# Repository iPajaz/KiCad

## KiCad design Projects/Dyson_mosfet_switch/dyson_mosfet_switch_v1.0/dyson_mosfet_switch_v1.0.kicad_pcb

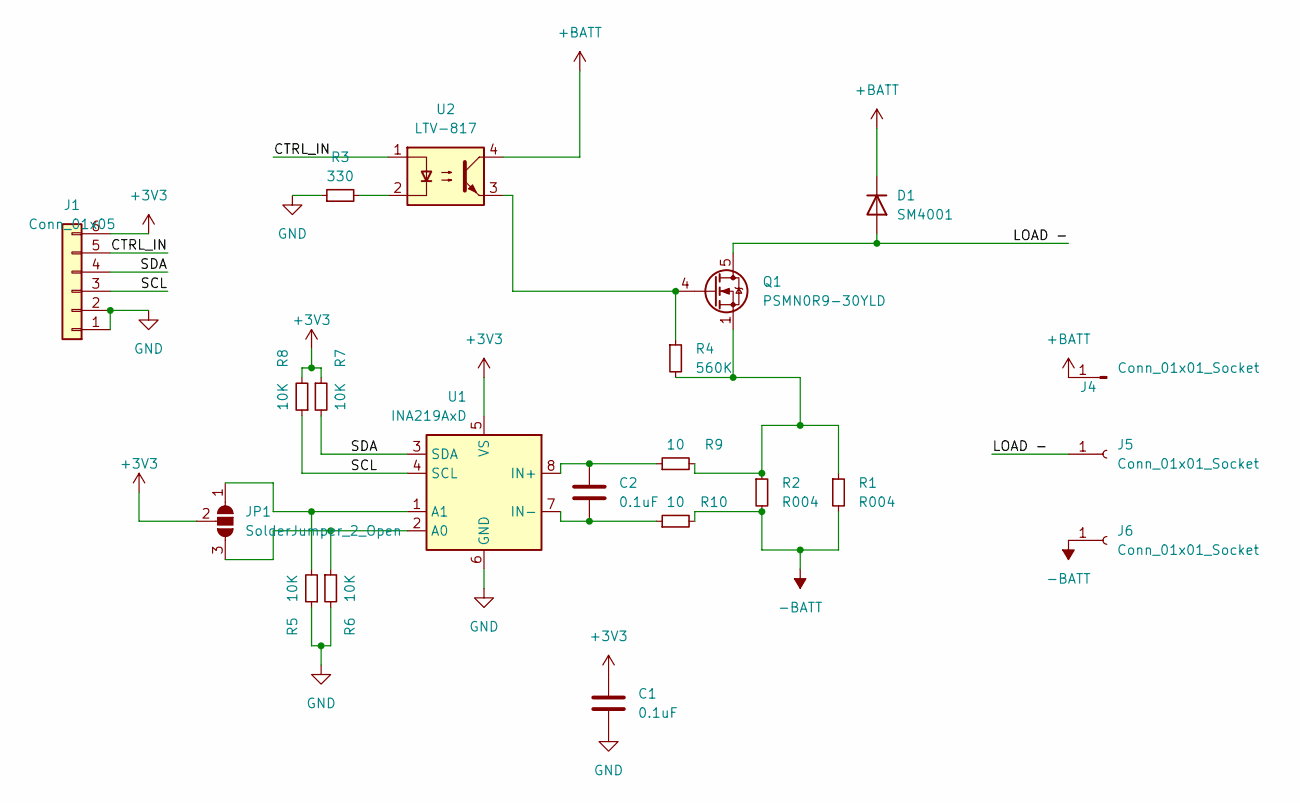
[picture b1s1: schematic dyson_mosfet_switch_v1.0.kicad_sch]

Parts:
C1, C2: 0.1uF; C_0805_2012Metric
D1: SM4001; D_SMA
J1: Conn_01x05; JST_PH_B6B-PH-K_1x06_P2.00mm_Vertical
J4: Conn_01x01_Socket; PinHeader_1x01_P2.54mm_Vertical
J5, J6: Conn_01x01_Socket; MountingHole_5mm_Pad_Via
JP1: SolderJumper_2_Open; SolderJumper-3_P1.3mm_Open_RoundedPad1.0x1.5mm
Q1: PSMN0R9-30YLD; LFPAK56
R1, R2: R004; R_2816_7142Metric
R3: 330; R_1206_3216Metric
R4: 560K; R_1206_3216Metric
R5, R6, R7, R8: 10K; R_1206_3216Metric
R9, R10: 10; R_1206_3216Metric
U1: INA219AxD; SOIC-8_3.9x4.9mm_P1.27mm
U2: LTV-817; DIP-4_W7.62mm

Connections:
+3V3: C1.1, J1.6, JP1.2 (C), R7.1, R8.2, U1.5 (VS)
+BATT: D1.1 (K), J4.1, U2.4
-BATT: J6.1, R1.2, R2.2, R10.2
/CTRL_IN: J1.5, U2.1
/LOAD -: D1.2 (A), J5.1, Q1.5 (D)
/SCL: J1.3, R8.1, U1.4 (SCL)
/SDA: J1.4, R7.2, U1.3 (SDA)
GND: C1.2, J1.1, J1.2, R3.1, R5.1, R6.2, U1.6 (GND)
unnamed: JP1.1 (A), R5.2, U1.1 (A1)
unnamed: JP1.3 (B), R6.1, U1.2 (A0)
unnamed: Q1.4 (G), R4.1, U2.3
unnamed: Q1.1 (S), Q1.2 (S), Q1.3 (S), R1.1, R2.1, R4.2, R9.2
unnamed: R3.2, U2.2
unnamed: C2.1, R9.1, U1.8 (IN+)
unnamed: C2.2, R10.1, U1.7 (IN-)

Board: 2 copper layers, 21 parts (0 on the bottom side), 15 nets, no tracks yet.

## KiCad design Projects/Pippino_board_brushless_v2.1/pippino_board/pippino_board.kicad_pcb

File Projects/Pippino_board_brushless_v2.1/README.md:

# Pippino II control PCB v2.1

## Main Features:

### Power supply

The board supports a 12 V power supply (within the range provided by a 3S Li-Ion battery), which is distributed to:
- A completely independent 3.3 V DC-DC converter providing always-on power supply, used to power the on-board E18 ZigBee module.
- A gated 12 V net, that can be switched on via a low on-resistance AO4409 MOSFET

The 12 V net, subsequently, provides power to:
- 4A, 5 V DC-DC converter used to output power to an external SBC (e.g. a Jetson Nano)
- 12 V output connector, to supply external peripherals, such as an USB splitter
- on board 3.3 V DC-DC converter, used to power the on-board ESP32-S3 microcontroller

### Always-on, low-power ZigBee module

The board includes an always-on ZigBee module, enabling the robot to be woken up via ZigBee/Home automation
while consuming low power (~10mA) when the system is powered off.
The ZigBee module can be programmed to perform more complex actions if required (GPIO pins exposed with a connector).

### ESP32-S3 microcontroller

The board includes an ESP32-S3 microcontroller with BT/WiFi capability. The ESP32 can be programmed via the USB3 connector,
which is intended to be always connected to the SBC.
OTA programming is then not required, as the SBC can be used to reprogram the ESP32 at any time.

The ESP32 is used to control the main driving motors for the robot, as well as receive information from sensors etc.

### Peripherals

The board includes:
- An ADC chip, connected via I2C to the MCU
- Smart DC-DC converters (TPS62110) with low battery voltage flagging capability (connected to a pin of the MCU)
- CP2102N USB to serial converter (for communication with the MCU)
- IO expansion IC connected via I2C + Interrupt

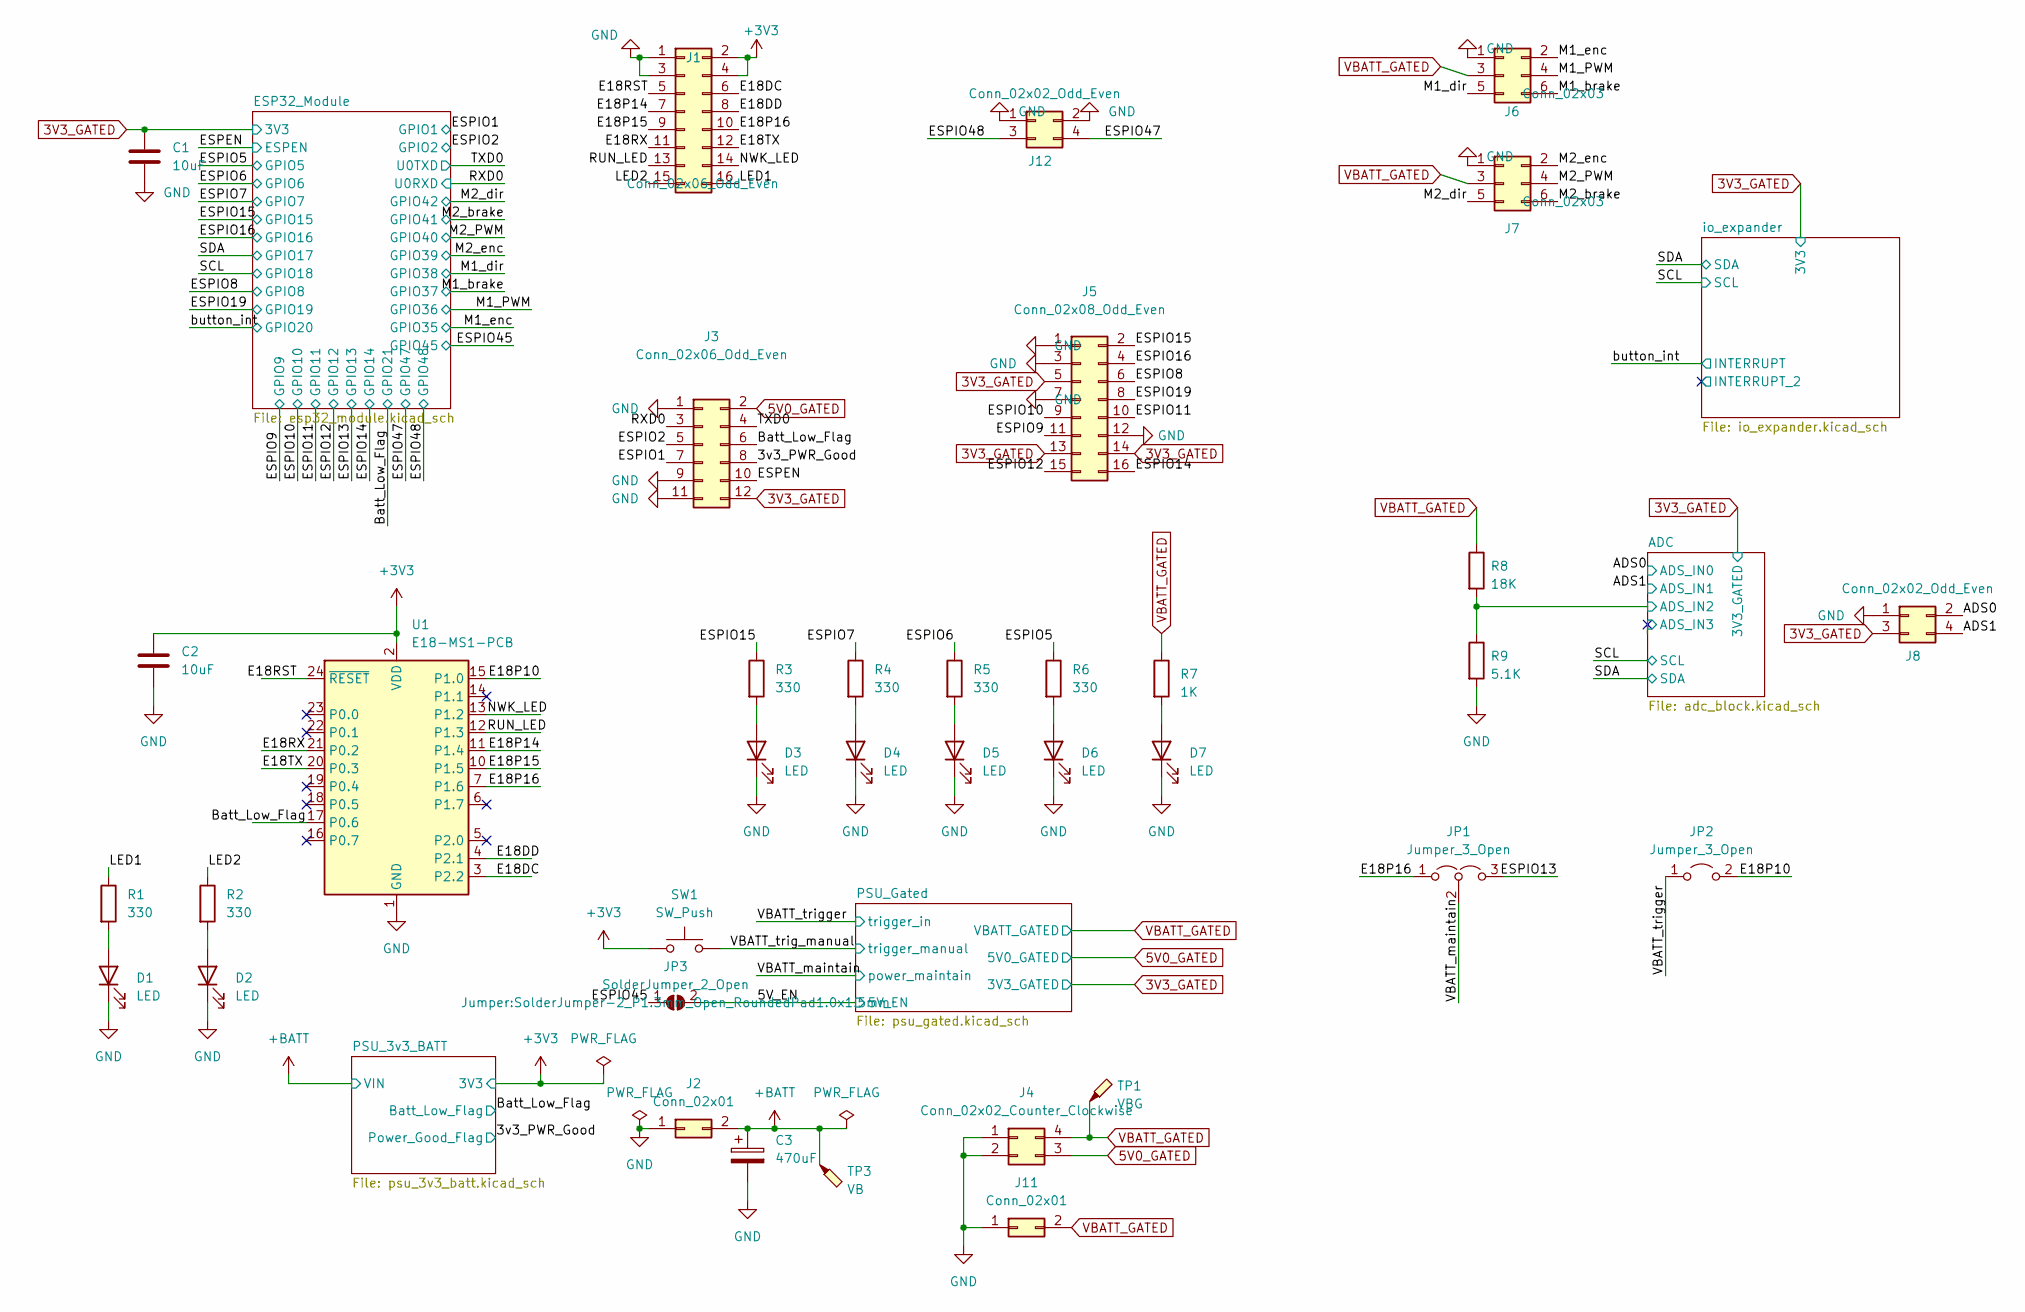
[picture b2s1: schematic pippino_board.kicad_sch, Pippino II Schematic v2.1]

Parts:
C1, C2: 10uF; C_0805_2012Metric
C3: 470uF; CP_Elec_10x10.5
D1, D2, D3, D4, D5, D6, D7: LED; LED_1206_3216Metric
J1: Conn_02x06_Odd_Even; PinHeader_2x08_P2.54mm_Vertical
J2, J11: Conn_02x01; Molex_Micro-Fit_3.0_43045-0200_2x01_P3.00mm_Horizontal
J3: Conn_02x06_Odd_Even; PinHeader_2x06_P2.54mm_Vertical
J4: Conn_02x02_Counter_Clockwise; Molex_Micro-Fit_3.0_43045-0400_2x02_P3.00mm_Horizontal
J5: Conn_02x08_Odd_Even; PinHeader_2x08_P2.54mm_Vertical
J6, J7: Conn_02x03; PinHeader_2x03_P2.54mm_Vertical
J8, J12: Conn_02x02_Odd_Even; PinHeader_2x02_P2.54mm_Vertical
JP1: Jumper_3_Open; PinHeader_1x03_P2.54mm_Vertical
JP2: Jumper_3_Open; PinHeader_1x02_P2.54mm_Vertical
JP3: SolderJumper_2_Open; SolderJumper-2_P1.3mm_Open_RoundedPad1.0x1.5mm
R1, R2, R3, R4, R5, R6: 330; R_1206_3216Metric
R7: 1K; R_1206_3216Metric
R8: 18K; R_1206_3216Metric
R9: 5.1K; R_1206_3216Metric
SW1: SW_Push; SW_SPST_CK_RS282G05A3
TP1: VBG; TestPoint_Pad_D1.5mm
TP3: VB; TestPoint_Pad_D1.5mm
U1: E18-MS1-PCB

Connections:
3V3_GATED: C1.1, J3.12, J5.5, J5.13, J5.14, J8.3; also elsewhere on the board
5V0_GATED: J3.2, J4.3; also elsewhere on the board
+3V3: C2.1, J1.2, J1.4, SW1.1, U1.2 (VDD); also elsewhere on the board
+BATT: C3.1, J2.2, TP3.1; also elsewhere on the board
/3v3_PWR_Good: J3.8; also elsewhere on the board
/5V_EN: JP3.2 (B); also elsewhere on the board
/ADC/ADS_IN2: R8.2, R9.1; also elsewhere on the board
/ADS0: J8.2; also elsewhere on the board
/ADS1: J8.4; also elsewhere on the board
/Batt_Low_Flag: J3.6, U1.17 (P0.6); also elsewhere on the board
/E18DC: J1.6, U1.3 (P2.2)
/E18DD: J1.8, U1.4 (P2.1)
/E18P10: JP2.2 (B), U1.15 (P1.0)
/E18P14: J1.7, U1.11 (P1.4)
/E18P15: J1.9, U1.10 (P1.5)
/E18P16: J1.10, JP1.1 (A), U1.7 (P1.6)
/E18RST: J1.5, U1.24 (~RESET)
/E18RX: J1.11, U1.21 (P0.2)
/E18TX: J1.12, U1.20 (P0.3)
/ESPEN: J3.10; also elsewhere on the board
/ESPIO1: J3.7; also elsewhere on the board
/ESPIO2: J3.5; also elsewhere on the board
/ESPIO5: R6.1; also elsewhere on the board
/ESPIO6: R5.1; also elsewhere on the board
/ESPIO7: R4.1; also elsewhere on the board
/ESPIO8: J5.6; also elsewhere on the board
/ESPIO9: J5.11; also elsewhere on the board
/ESPIO10: J5.9; also elsewhere on the board
/ESPIO11: J5.10; also elsewhere on the board
/ESPIO12: J5.15; also elsewhere on the board
/ESPIO13: JP1.3 (B); also elsewhere on the board
/ESPIO14: J5.16; also elsewhere on the board
/ESPIO15: J5.2, R3.1; also elsewhere on the board
/ESPIO16: J5.4; also elsewhere on the board
/ESPIO19: J5.8; also elsewhere on the board
/ESPIO45: JP3.1 (A); also elsewhere on the board
/ESPIO47: J12.4; also elsewhere on the board
/ESPIO48: J12.3; also elsewhere on the board
/LED1: J1.16, R1.1
/LED2: J1.15, R2.1
/M1_PWM: J6.4; also elsewhere on the board
/M1_brake: J6.6; also elsewhere on the board
/M1_dir: J6.5; also elsewhere on the board
/M1_enc: J6.2; also elsewhere on the board
/M2_PWM: J7.4; also elsewhere on the board
/M2_brake: J7.6; also elsewhere on the board
/M2_dir: J7.5; also elsewhere on the board
/M2_enc: J7.2; also elsewhere on the board
/NWK_LED: J1.14, U1.13 (P1.2)
/RUN_LED: J1.13, U1.12 (P1.3)
/RXD0: J3.3; also elsewhere on the board
/TXD0: J3.4; also elsewhere on the board
/VBATT_maintain: JP1.2 (C); also elsewhere on the board
/VBATT_trig_manual: SW1.2; also elsewhere on the board
/VBATT_trigger: JP2.1 (A); also elsewhere on the board
unnamed: D1.2 (A), R1.2
unnamed: D2.2 (A), R2.2
unnamed: D3.2 (A), R3.2
unnamed: D4.2 (A), R4.2
unnamed: D5.2 (A), R5.2
unnamed: D6.2 (A), R6.2
unnamed: D7.2 (A), R7.2
VBATT_GATED: J4.4, J6.3, J7.3, J11.2, R7.1, R8.1, TP1.1; also elsewhere on the board

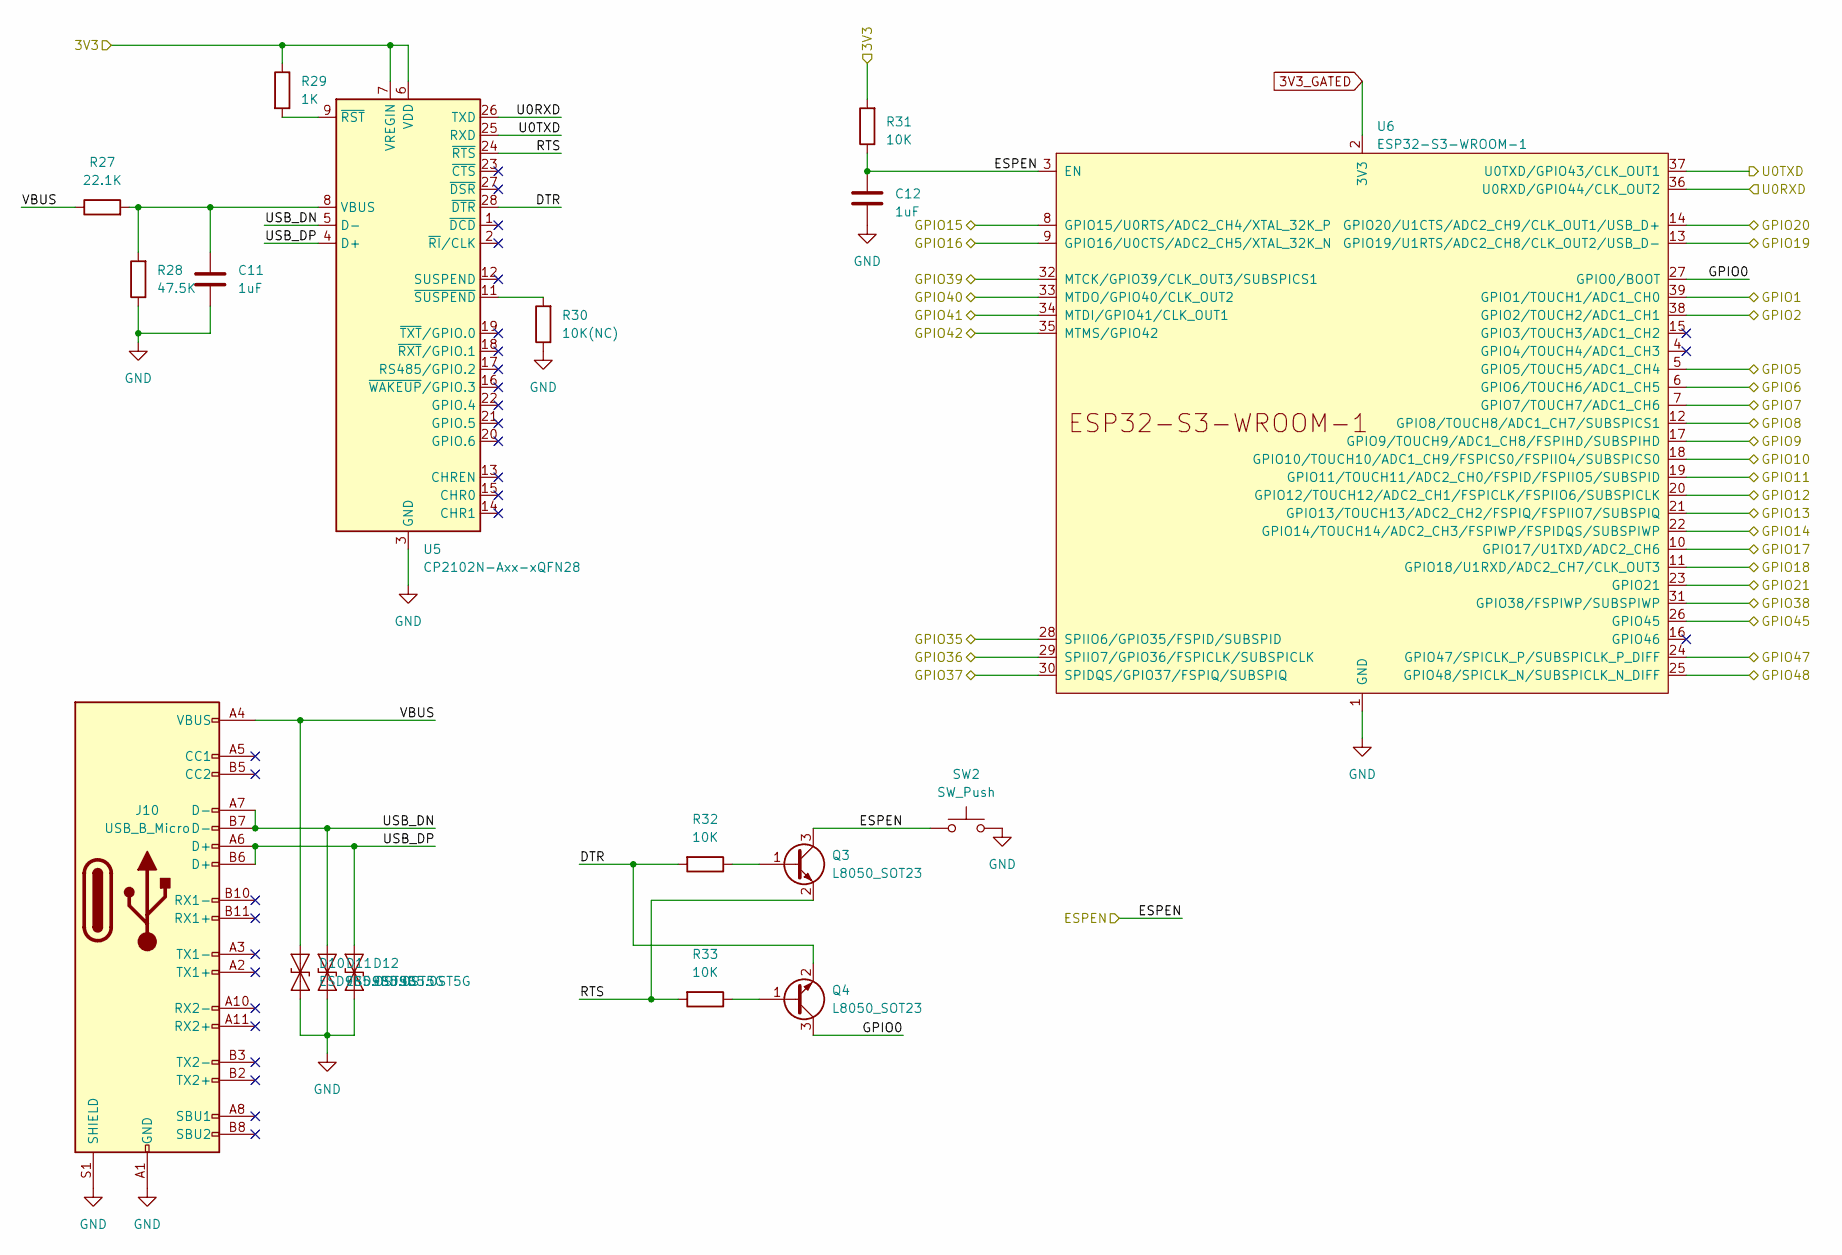
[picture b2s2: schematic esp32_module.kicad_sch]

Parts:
C11, C12: 1uF; C_0805_2012Metric
D10, D11, D12: ESD9B5.0ST5G; D_SOD-523
J10: USB_B_Micro; USB_C_Receptacle_Amphenol_12401610E4-2A
Q3, Q4: L8050_SOT23; SOT-23
R27: 22.1K; R_1206_3216Metric
R28: 47.5K; R_1206_3216Metric
R29: 1K; R_1206_3216Metric
R30: 10K(NC); R_1206_3216Metric
R31, R32, R33: 10K; R_1206_3216Metric
SW2: SW_Push; SW_SPST_CK_RS282G05A3
U5: CP2102N-Axx-xQFN28; QFN-28-1EP_5x5mm_P0.5mm_EP3.35x3.35mm
U6: ESP32-S3-WROOM-1

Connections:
3V3_GATED: R29.1, R31.2, U5.6 (VDD), U5.7 (VREGIN), U6.2 (3V3); also elsewhere on the board
/Batt_Low_Flag: U6.23 (GPIO21); also elsewhere on the board
/ESP32_Module/DTR: Q4.2 (E), R32.2, U5.28 (~DTR)
/ESP32_Module/GPIO0: Q4.3 (C), U6.27 (GPIO0/BOOT)
/ESP32_Module/RTS: Q3.2 (E), R33.2, U5.24 (~RTS)
/ESP32_Module/USB_DN: D11.1 (A1), J10.A7 (D-), J10.B7 (D-), U5.5 (D-)
/ESP32_Module/USB_DP: D12.1 (A1), J10.A6 (D+), J10.B6 (D+), U5.4 (D+)
/ESP32_Module/VBUS: D10.1 (A1), J10.A4 (VBUS), J10.A9 (VBUS), J10.B4 (VBUS), J10.B9 (VBUS), R27.1
/ESPEN: C12.1, Q3.3 (C), R31.1, SW2.1, U6.3 (EN); also elsewhere on the board
/ESPIO1: U6.39 (GPIO1/TOUCH1/ADC1_CH0); also elsewhere on the board
/ESPIO2: U6.38 (GPIO2/TOUCH2/ADC1_CH1); also elsewhere on the board
/ESPIO5: U6.5 (GPIO5/TOUCH5/ADC1_CH4); also elsewhere on the board
/ESPIO6: U6.6 (GPIO6/TOUCH6/ADC1_CH5); also elsewhere on the board
/ESPIO7: U6.7 (GPIO7/TOUCH7/ADC1_CH6); also elsewhere on the board
/ESPIO8: U6.12 (GPIO8/TOUCH8/ADC1_CH7/SUBSPICS1); also elsewhere on the board
/ESPIO9: U6.17 (GPIO9/TOUCH9/ADC1_CH8/FSPIHD/SUBSPIHD); also elsewhere on the board
/ESPIO10: U6.18 (GPIO10/TOUCH10/ADC1_CH9/FSPICS0/FSPIIO4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); also elsewhere on the board
/ESPIO11: U6.19 (GPIO11/TOUCH11/ADC2_CH0/FSPID/FSPIIO5/S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); also elsewhere on the board
/ESPIO12: U6.20 (GPIO12/TOUCH12/ADC2_CH1/FSPICLK/FSPIIO6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); also elsewhere on the board
/ESPIO13: U6.21 (GPIO13/TOUCH13/ADC2_CH2/FSPIQ/FSPIIO7/S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); also elsewhere on the board
/ESPIO14: U6.22 (GPIO14/TOUCH14/ADC2_CH3/FSPIWP/FSPIDQS/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); also elsewhere on the board
/ESPIO15: U6.8 (GPIO15/U0RTS/ADC2_CH4/XTAL_32K_P); also elsewhere on the board
/ESPIO16: U6.9 (GPIO16/U0CTS/ADC2_CH5/XTAL_32K_N); also elsewhere on the board
/ESPIO19: U6.13 (GPIO19/U1RTS/ADC2_CH8/CLK_OUT2/USB_D-); also elsewhere on the board
/ESPIO45: U6.26 (GPIO45); also elsewhere on the board
/ESPIO47: U6.24 (GPIO47/SPICLK_P/SUBSPICLK_P_DIFF); also elsewhere on the board
/ESPIO48: U6.25 (GPIO48/SPICLK_N/SUBSPICLK_N_DIFF); also elsewhere on the board
/M1_PWM: U6.29 (SPIIO7/GPIO36/FSPICLK/SUBSPICLK); also elsewhere on the board
/M1_brake: U6.30 (SPIDQS/GPIO37/FSPIQ/SUBSPIQ); also elsewhere on the board
/M1_dir: U6.31 (GPIO38/FSPIWP/SUBSPIWP); also elsewhere on the board
/M1_enc: U6.28 (SPIIO6/GPIO35/FSPID/SUBSPID); also elsewhere on the board
/M2_PWM: U6.33 (MTDO/GPIO40/CLK_OUT2); also elsewhere on the board
/M2_brake: U6.34 (MTDI/GPIO41/CLK_OUT1); also elsewhere on the board
/M2_dir: U6.35 (MTMS/GPIO42); also elsewhere on the board
/M2_enc: U6.32 (MTCK/GPIO39/CLK_OUT3/SUBSPICS1); also elsewhere on the board
/RXD0: U5.26 (TXD), U6.36 (U0RXD/GPIO44/CLK_OUT2); also elsewhere on the board
/SCL: U6.11 (GPIO18/U1RXD/ADC2_CH7/CLK_OUT3); also elsewhere on the board
/SDA: U6.10 (GPIO17/U1TXD/ADC2_CH6); also elsewhere on the board
/TXD0: U5.25 (RXD), U6.37 (U0TXD/GPIO43/CLK_OUT1); also elsewhere on the board
/button_int: U6.14 (GPIO20/U1CTS/ADC2_CH9/CLK_OUT1/USB_D+); also elsewhere on the board
unnamed: Q3.1 (B), R32.1
unnamed: Q4.1 (B), R33.1
unnamed: C11.1, R27.2, R28.2, U5.8 (VBUS)
unnamed: R29.2, U5.9 (~RST)
unnamed: R30.2, U5.11 (~SUSPEND)

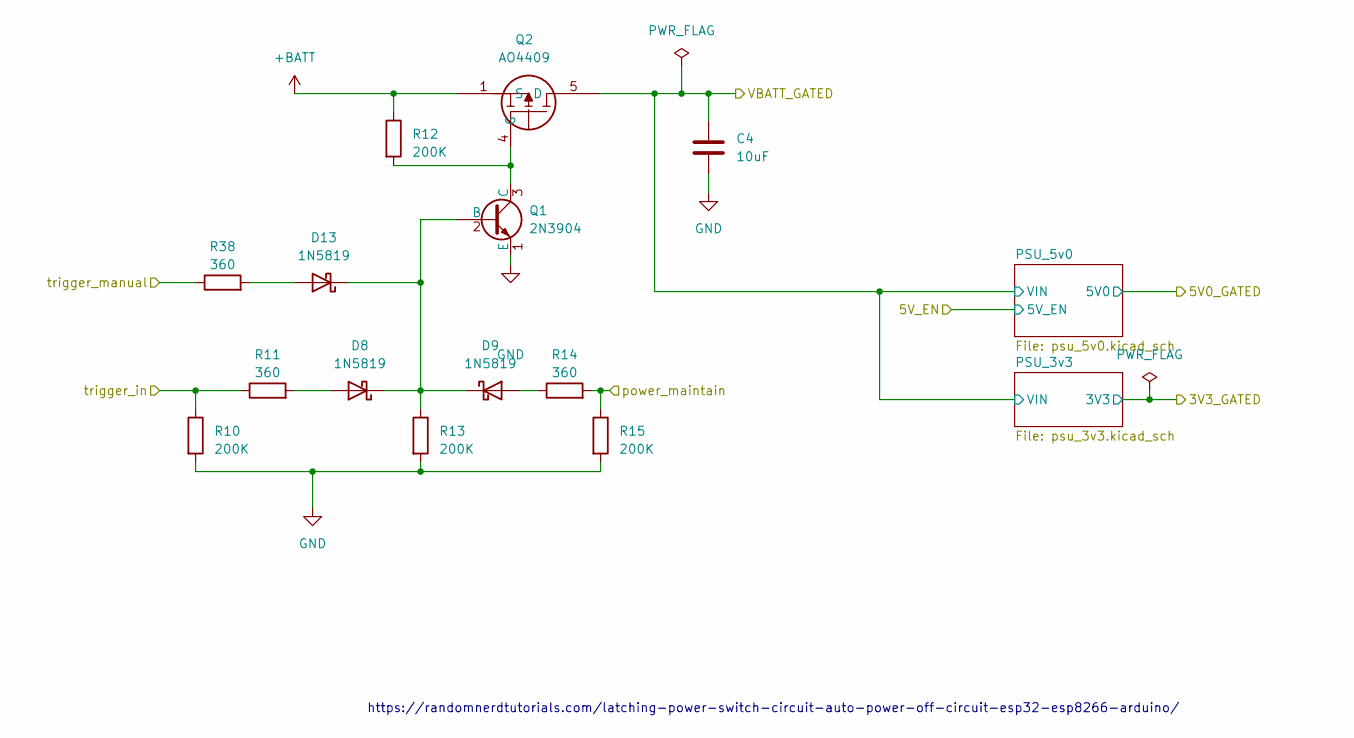
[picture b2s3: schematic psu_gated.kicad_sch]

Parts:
C4: 10uF; C_0805_2012Metric
D8, D9, D13: 1N5819; D_SOD-123
Q1: 2N3904; 2N3904_SOT-23
Q2: AO4409; SOIC-8_3.9x4.9mm_P1.27mm
R10, R12, R13, R15: 200K; R_1206_3216Metric
R11, R14, R38: 360; R_1206_3216Metric

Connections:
+BATT: Q2.1 (S), Q2.2 (S), Q2.3 (S), R12.1; also elsewhere on the board
/VBATT_maintain: R14.2, R15.1; also elsewhere on the board
/VBATT_trig_manual: R38.1; also elsewhere on the board
/VBATT_trigger: R10.1, R11.1; also elsewhere on the board
unnamed: D8.2 (A), R11.2
unnamed: D9.2 (A), R14.1
unnamed: D13.2 (A), R38.2
unnamed: D8.1 (K), D9.1 (K), D13.1 (K), Q1.2 (B), R13.1
unnamed: Q1.3 (C), Q2.4 (G), R12.2
VBATT_GATED: C4.1, Q2.5 (D), Q2.6 (D), Q2.7 (D), Q2.8 (D); also elsewhere on the board

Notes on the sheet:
https://randomnerdtutorials.com/latching-power-switch-circuit-auto-power-off-circuit-esp32-esp8266-arduino/

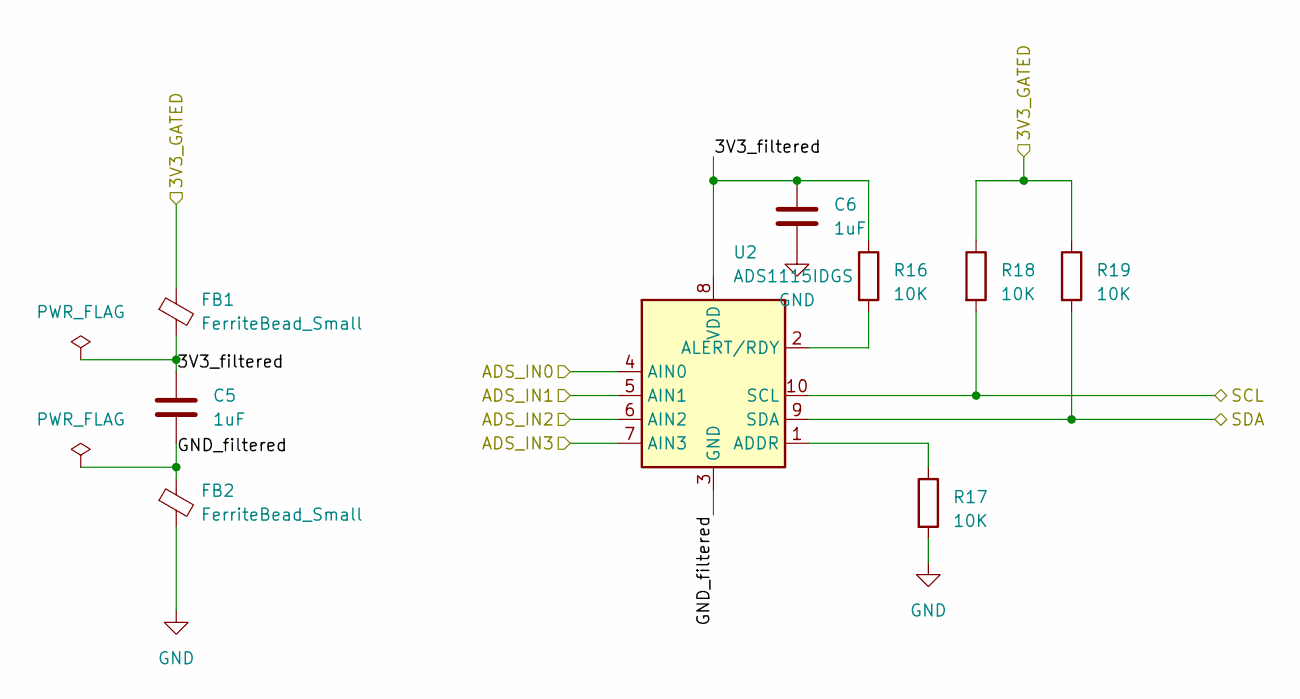
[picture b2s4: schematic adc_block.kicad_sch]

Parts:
C5, C6: 1uF; C_0805_2012Metric
FB1, FB2: FerriteBead_Small; C_0805_2012Metric
R16, R17, R18, R19: 10K; R_1206_3216Metric
U2: ADS1115IDGS; VSSOP-10_3x3mm_P0.5mm

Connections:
3V3_GATED: FB1.1, R18.1, R19.1; also elsewhere on the board
/ADC/3V3_filtered: C5.1, C6.1, FB1.2, R16.1, U2.8 (VDD)
/ADC/ADS_IN2: U2.6 (AIN2); also elsewhere on the board
/ADC/ADS_IN3: U2.7 (AIN3)
/ADC/GND_filtered: C5.2, FB2.1, U2.3 (GND)
/ADS0: U2.4 (AIN0); also elsewhere on the board
/ADS1: U2.5 (AIN1); also elsewhere on the board
/SCL: R18.2, U2.10 (SCL); also elsewhere on the board
/SDA: R19.2, U2.9 (SDA); also elsewhere on the board
unnamed: R17.1, U2.1 (ADDR)
unnamed: R16.2, U2.2 (ALERT/RDY)

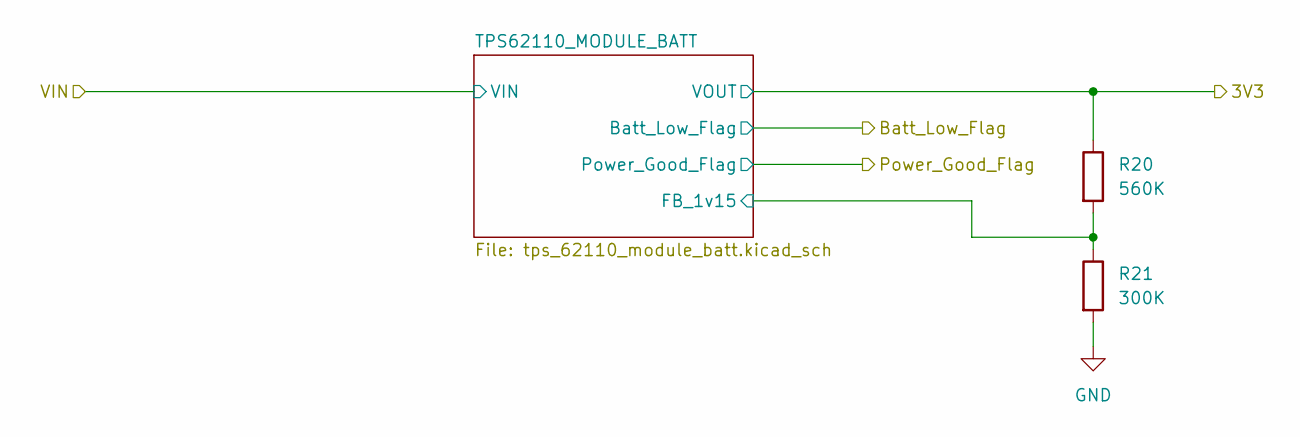
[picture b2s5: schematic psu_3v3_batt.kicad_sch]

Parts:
R20: 560K; R_1206_3216Metric
R21: 300K; R_1206_3216Metric

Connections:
+3V3: R20.1; also elsewhere on the board
/PSU_3v3_BATT/TPS62110_MODULE_BATT/FB_1v15: R20.2, R21.1; also elsewhere on the board

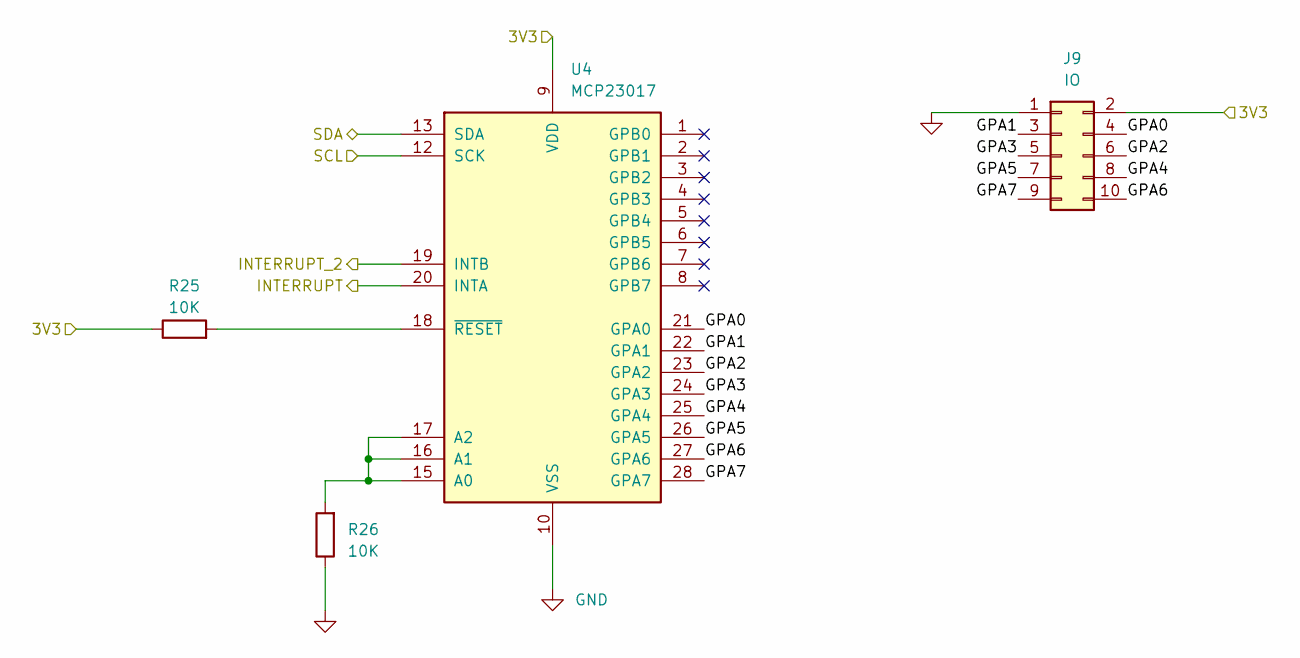
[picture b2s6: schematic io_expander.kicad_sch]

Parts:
J9: IO; PinHeader_2x05_P2.54mm_Vertical
R25, R26: 10K; R_1206_3216Metric
U4: MCP23017; SSOP-28_5.3x10.2mm_P0.65mm

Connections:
3V3_GATED: J9.2, R25.1, U4.9 (VDD); also elsewhere on the board
/SCL: U4.12 (SCK); also elsewhere on the board
/SDA: U4.13 (SDA); also elsewhere on the board
/button_int: U4.20 (INTA); also elsewhere on the board
/io_expander/GPA0: J9.4, U4.21 (GPA0)
/io_expander/GPA1: J9.3, U4.22 (GPA1)
/io_expander/GPA2: J9.6, U4.23 (GPA2)
/io_expander/GPA3: J9.5, U4.24 (GPA3)
/io_expander/GPA4: J9.8, U4.25 (GPA4)
/io_expander/GPA5: J9.7, U4.26 (GPA5)
/io_expander/GPA6: J9.10, U4.27 (GPA6)
/io_expander/GPA7: J9.9, U4.28 (GPA7)
/io_expander/INTERRUPT_2: U4.19 (INTB)
unnamed: R26.2, U4.15 (A0), U4.16 (A1), U4.17 (A2)
unnamed: R25.2, U4.18 (~RESET)

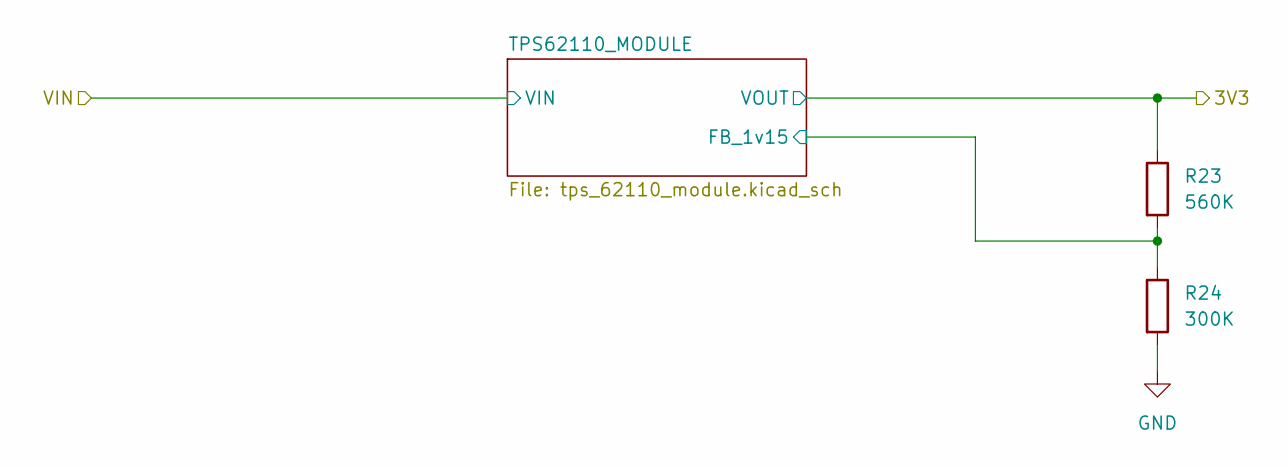
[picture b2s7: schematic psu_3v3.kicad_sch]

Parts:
R23: 560K; R_1206_3216Metric
R24: 300K; R_1206_3216Metric

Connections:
3V3_GATED: R23.1; also elsewhere on the board
/PSU_Gated/PSU_3v3/TPS62110_MODULE/FB_1v15: R23.2, R24.1; also elsewhere on the board

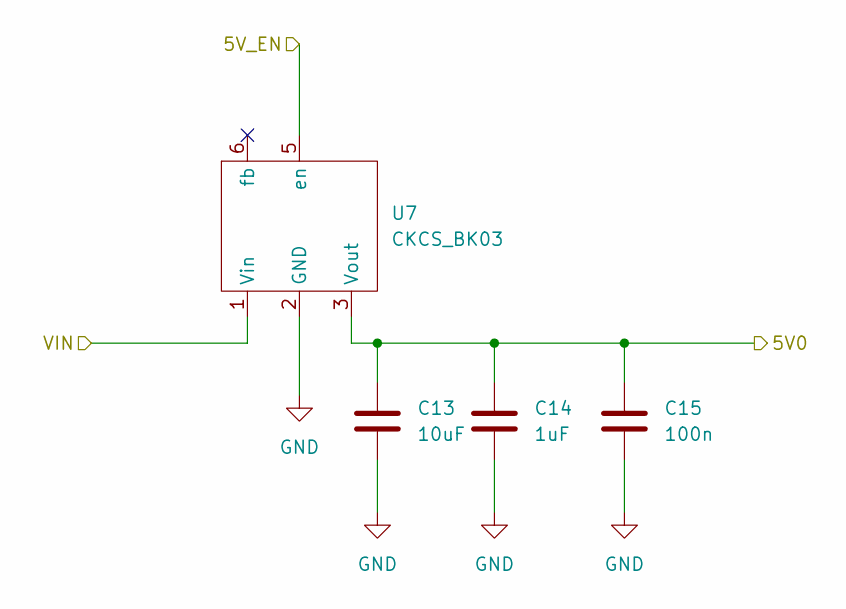
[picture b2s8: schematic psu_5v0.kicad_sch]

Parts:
C13: 10uF; C_0805_2012Metric
C14: 1uF; C_0805_2012Metric
C15: 100n; C_0805_2012Metric
U7: CKCS_BK03; CKCS-BK03

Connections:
5V0_GATED: C13.1, C14.1, C15.1, U7.3 (Vout); also elsewhere on the board
/5V_EN: U7.5 (en); also elsewhere on the board
VBATT_GATED: U7.1 (Vin); also elsewhere on the board

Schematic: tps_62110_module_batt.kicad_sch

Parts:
C16: 10uF; C_0805_2012Metric
C17: 1uF; C_0805_2012Metric
C18: 10p; C_0805_2012Metric
C19: 22uF; C_1206_3216Metric
C20: 100n; C_0805_2012Metric
L2: 6.8u 2A; inductor_smd_5.8x4.5mm
R34: 680K; R_1206_3216Metric
R35: 100K; R_1206_3216Metric
R36, R37: 1M; R_1206_3216Metric
U8: TPS62110; Texas_S-PVQFN-N16_EP2.7x2.7mm_ThermalVias

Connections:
+3V3: C18.1, C19.1, C20.1, L2.2, R36.1, R37.1; also elsewhere on the board
+BATT: C16.1, C17.1, R34.1, U8.2 (VIN), U8.3 (VIN), U8.4 (EN), U8.8 (VINA); also elsewhere on the board
/3v3_PWR_Good: R36.2, U8.13 (PG); also elsewhere on the board
/Batt_Low_Flag: R34.2, R35.1, R37.2, U8.6 (LBO), U8.7 (LBI); also elsewhere on the board
/PSU_3v3_BATT/TPS62110_MODULE_BATT/FB_1v15: C18.2, U8.10 (FB); also elsewhere on the board
unnamed: L2.1, U8.14 (SW), U8.15 (SW)

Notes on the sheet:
Battery low triggers at: 1.256V/100K*(680K+100K) = 9.8 V

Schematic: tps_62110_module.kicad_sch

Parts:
C7: 10uF; C_0805_2012Metric
C8: 1uF; C_0805_2012Metric
C9: 10p; C_0805_2012Metric
C10: 22uF; C_1206_3216Metric
L1: 6.8u 2A; inductor_smd_5.8x4.5mm
R22: 1M; R_1206_3216Metric
U3: TPS62110; Texas_S-PVQFN-N16_EP2.7x2.7mm_ThermalVias

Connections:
3V3_GATED: C9.1, C10.1, L1.2, R22.1; also elsewhere on the board
/PSU_Gated/PSU_3v3/TPS62110_MODULE/FB_1v15: C9.2, U3.10 (FB); also elsewhere on the board
unnamed: L1.1, U3.14 (SW), U3.15 (SW)
unnamed: R22.2, U3.13 (PG)
VBATT_GATED: C7.1, C8.1, U3.2 (VIN), U3.3 (VIN), U3.4 (EN), U3.8 (VINA); also elsewhere on the board

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
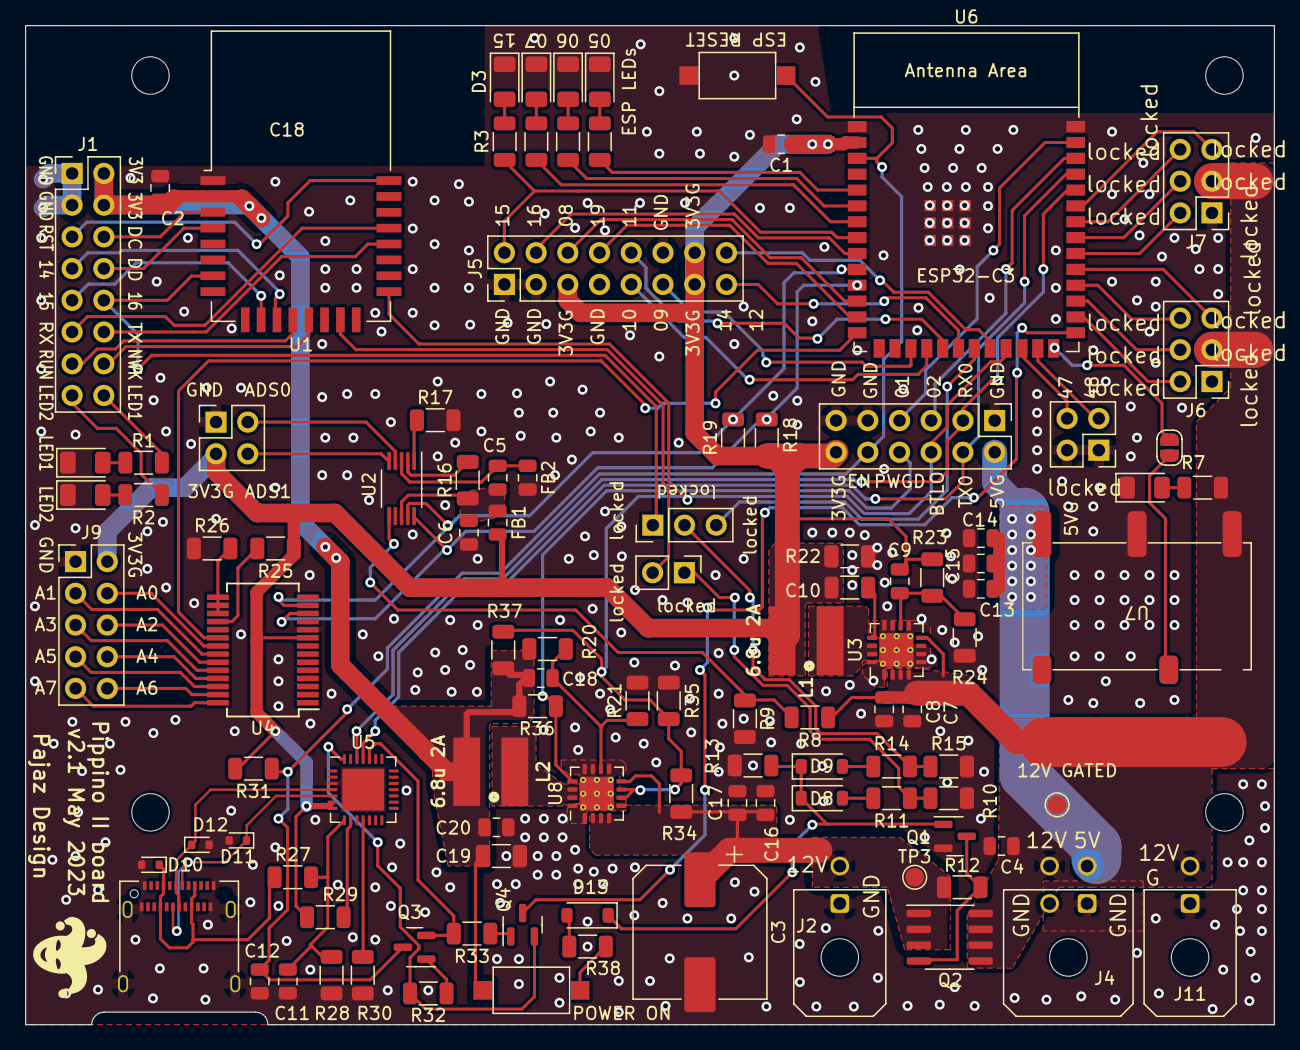
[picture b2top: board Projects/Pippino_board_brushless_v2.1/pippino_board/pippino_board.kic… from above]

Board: 2 copper layers, 100.0 x 80.0 mm, 110 parts (0 on the bottom side), 102 nets.

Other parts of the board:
MH3, MH3#2, MH3#3, MH3#4: MountingHole_3mm
